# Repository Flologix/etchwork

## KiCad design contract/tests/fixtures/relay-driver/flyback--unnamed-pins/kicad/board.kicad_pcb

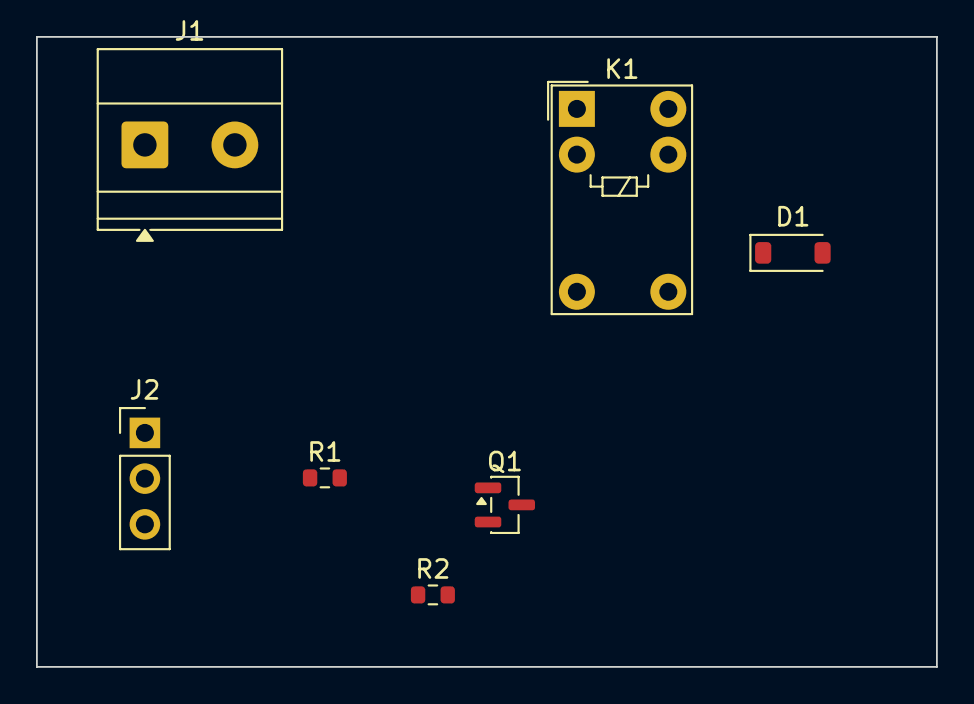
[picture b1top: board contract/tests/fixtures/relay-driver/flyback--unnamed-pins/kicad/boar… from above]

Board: 2 copper layers, 50.0 x 35.0 mm, 7 parts (0 on the bottom side), 5 nets, no tracks yet.

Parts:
D1: 1N4148W; D_SOD-123
J1: Screw_Terminal_01x02; TerminalBlock_Phoenix_MKDS-1,5-2_1x02_P5.00mm_Horizontal
J2: Conn_01x03; PinHeader_1x03_P2.54mm_Vertical
K1: G5V-1; Relay_SPDT_Omron_G5V-1
Q1: AO3400A; SOT-23
R1: 100; R_0603_1608Metric
R2: 100k; R_0603_1608Metric

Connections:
+12V: D1.1, J1.1, K1.1
GND: J1.2, J2.1, Q1.2 (S), R2.2
N_DRAIN: D1.2, K1.10, Q1.3 (D)
N_GATE: Q1.1 (G), R1.2, R2.1
N_SIG: J2.2, R1.1

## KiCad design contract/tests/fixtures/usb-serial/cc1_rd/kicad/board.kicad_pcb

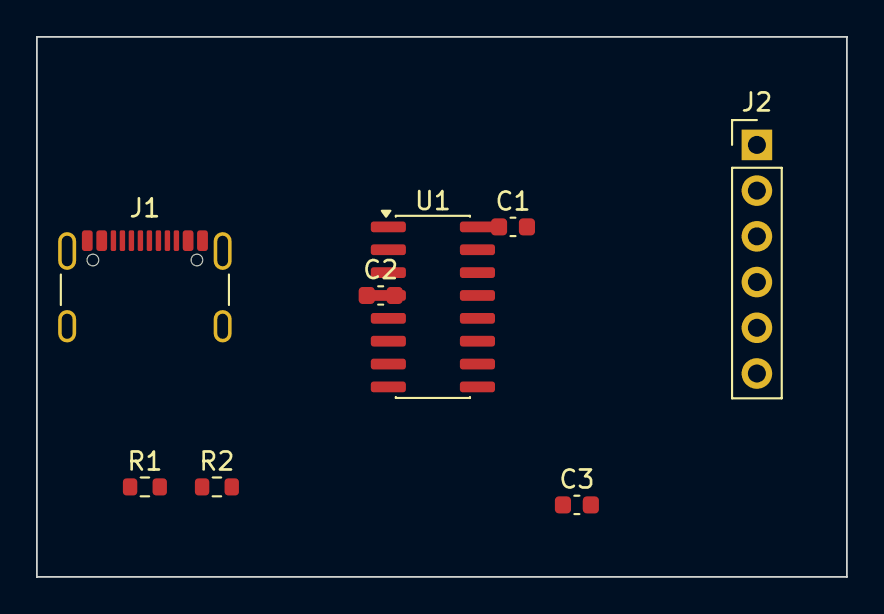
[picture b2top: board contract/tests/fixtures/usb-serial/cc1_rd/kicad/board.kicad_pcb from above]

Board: 2 copper layers, 45.0 x 30.0 mm, 8 parts (0 on the bottom side), 11 nets, no tracks yet.

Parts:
C1, C2, C3: 100n; C_0603_1608Metric
J1: USB_C_Receptacle_USB2.0_16P; USB_C_Receptacle_GCT_USB4105-xx-A_16P_TopMnt_Horizontal
J2: Conn_01x06; PinHeader_1x06_P2.54mm_Vertical
R1: 10k; R_0603_1608Metric
R2: 5.1k; R_0603_1608Metric
U1: CH340C; SOIC-16_3.9x9.9mm_P1.27mm

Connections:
CC1: J1.A5 (CC1), R1.1
CC2: J1.B5 (CC2), R2.1
D+: J1.A6 (D+), J1.B6 (D+), U1.5 (UD+)
D-: J1.A7 (D-), J1.B7 (D-), U1.6 (UD-)
GND: C1.2, C2.2, J1.A1 (GND), J1.A12 (GND), J1.B1 (GND), J1.B12 (GND), J1.SH (SHIELD), J2.1, R1.2, R2.2, U1.1 (GND)
N_DTR: C3.1, U1.13 (~DTR)
N_RST: C3.2, J2.6
N_RX: J2.5, U1.3 (RXD)
N_TX: J2.4, U1.2 (TXD)
N_V3: C2.1, U1.4 (V3)
VBUS: C1.1, J1.A4 (VBUS), J1.A9 (VBUS), J1.B4 (VBUS), J1.B9 (VBUS), J2.3, U1.16 (VCC)
